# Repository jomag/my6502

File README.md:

# My 6502

I started watching [Ben Eaters](https://eater.net) [video series](https://eater.net/8bit)
where he builds a 6502 (actually, 65C02) based 8-bit computer from scratch
on breadboards. I thought it could be fun to follow along and build something similar,
but using real PCB's cause breadboards drive me crazy.

It might end up being something pretty to hang on the wall...

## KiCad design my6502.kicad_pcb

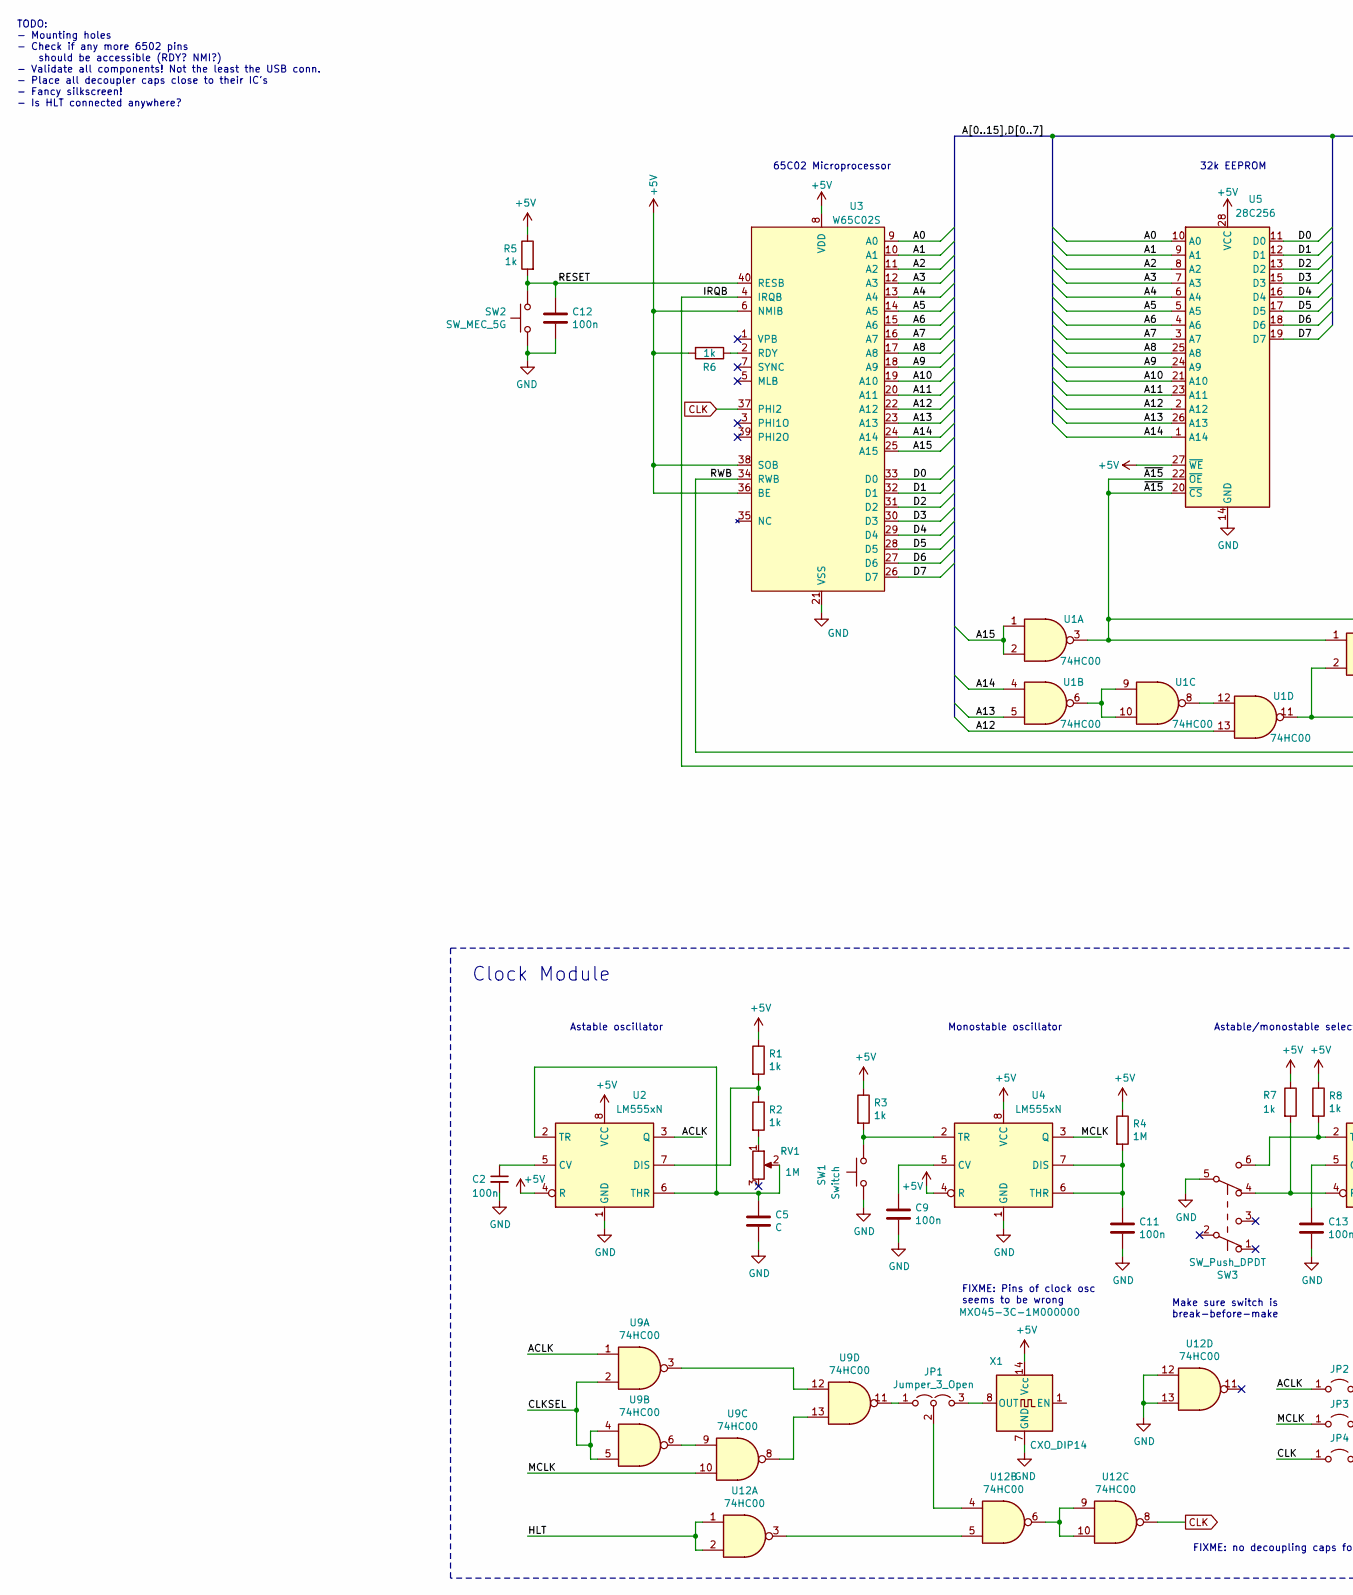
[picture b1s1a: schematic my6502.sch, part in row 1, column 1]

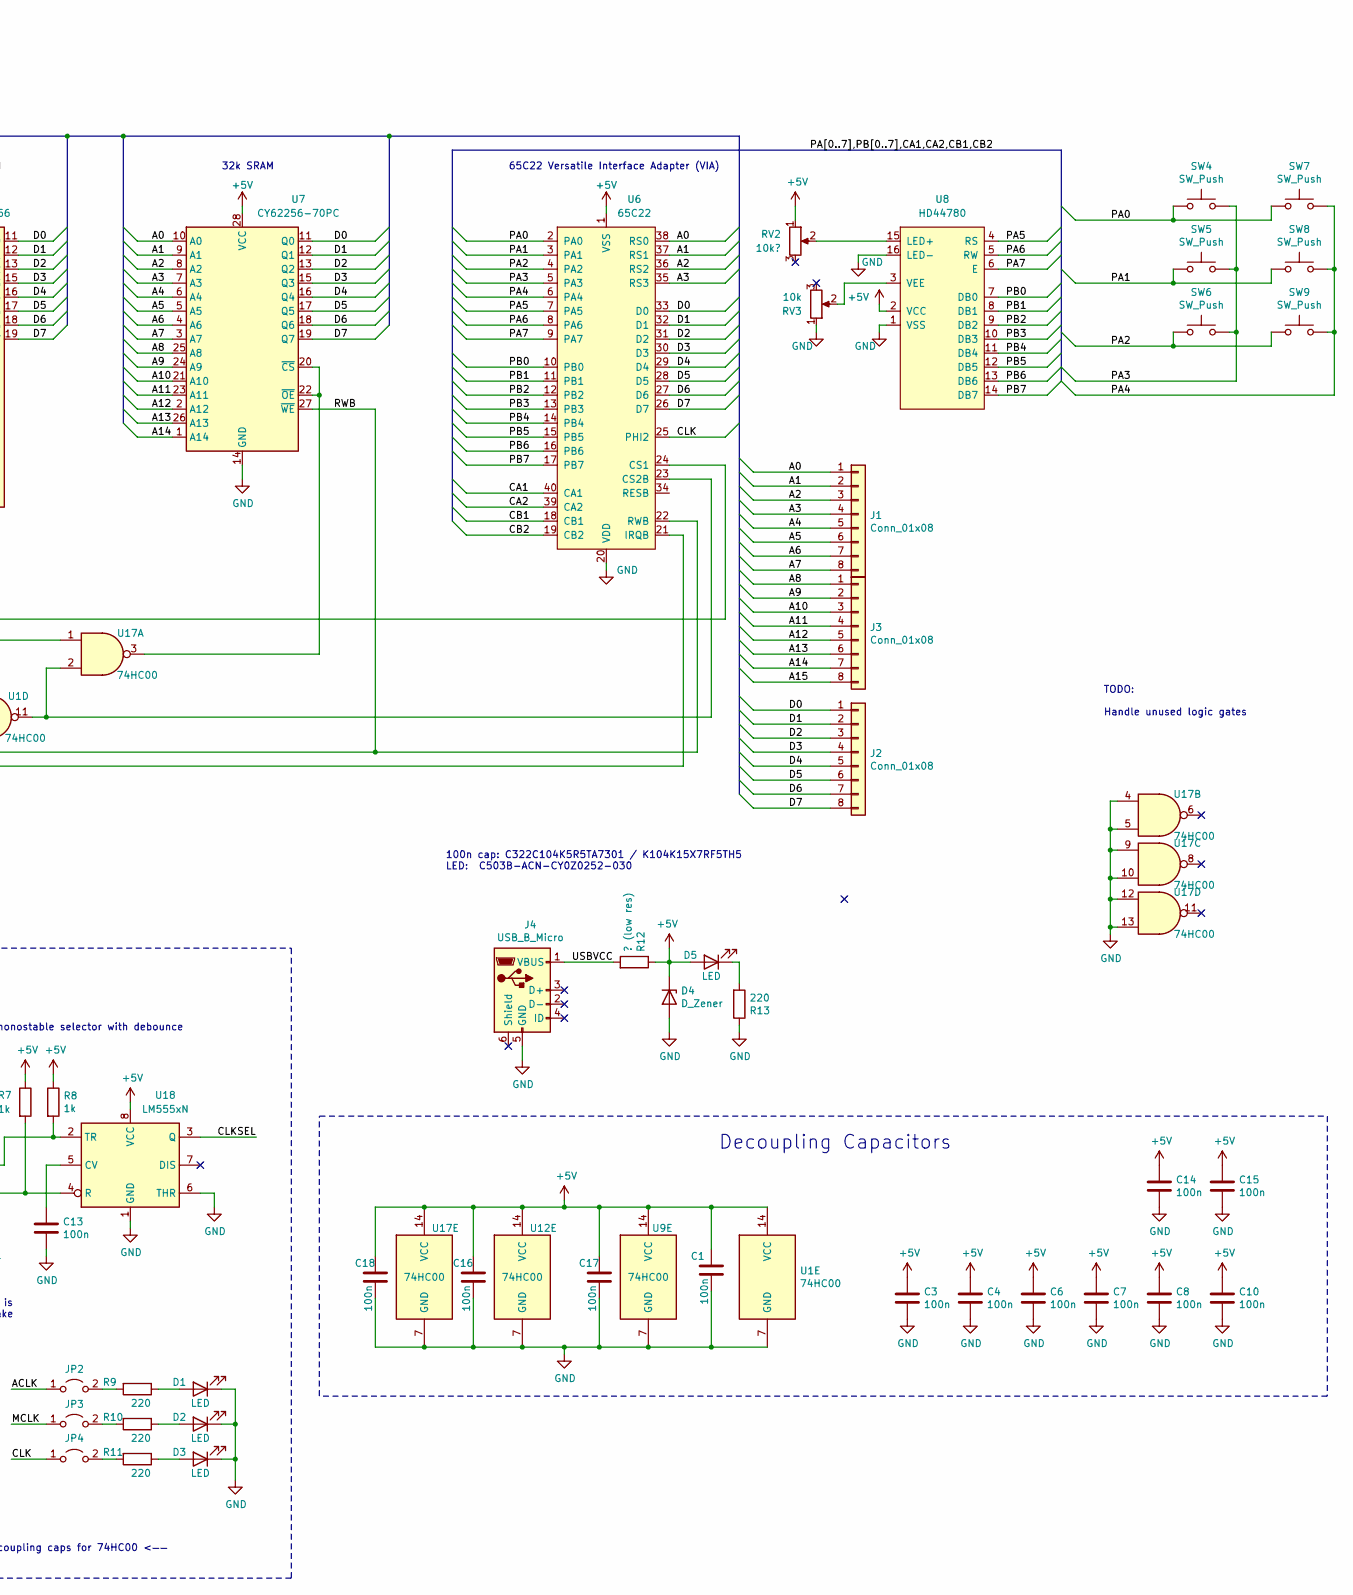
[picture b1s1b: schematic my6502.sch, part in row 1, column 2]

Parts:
C1, C2, C3, C4, C6, C7, C8, C9, C10, C11, C12, C13, C14, C15, C16, C17, C18: 100n; C_Disc_D5.1mm_W3.2mm_P5.00mm
C5: C
D1, D2, D3, D5: LED; LED_D3.0mm
D4: D_Zener; D_A-405_P7.62mm_Horizontal
J1, J2, J3: Conn_01x08; PinHeader_1x08_P2.54mm_Vertical
J4: USB_B_Micro; USB_Micro-B_Molex_47346-0001
JP1: Jumper_3_Open; PinHeader_1x03_P2.54mm_Vertical
JP2, JP3, JP4: Jumper_2_Open; PinHeader_1x02_P2.54mm_Vertical
R1, R2, R3, R5, R6, R7, R8: 1k; R_Axial_DIN0207_L6.3mm_D2.5mm_P7.62mm_Horizontal
R4: 1M; R_Axial_DIN0207_L6.3mm_D2.5mm_P7.62mm_Horizontal
R9, R10, R11, R13: 220; R_Axial_DIN0207_L6.3mm_D2.5mm_P7.62mm_Horizontal
R12: ? (low res); R_Axial_DIN0207_L6.3mm_D2.5mm_P7.62mm_Horizontal
RV1: 1M; Potentiometer_Bourns_3386F_Vertical; Digi-Key 3386X-1-105TLF-ND
RV2: 10k?; Potentiometer_Bourns_3296W_Vertical
RV3: 10k; Potentiometer_Bourns_3296W_Vertical
SW1: Switch; SW_PUSH_6mm
SW2: SW_MEC_5G; SW_PUSH_6mm
SW3: SW_Push_DPDT
SW4: SW_Push; SW_PUSH_6mm; PartID Adafruit 4183
SW5, SW6, SW7, SW8, SW9: SW_Push; SW_PUSH_6mm
U1, U9, U12, U17: 74HC00; DIP-14_W7.62mm_LongPads
U2, U4, U18: LM555xN; DIP-8_W7.62mm
U3: W65C02S; DIP-40_W15.24mm_Socket_LongPads
U5: 28C256; DIP-28_W15.24mm_Socket_LongPads
U6: 65C22; DIP-40_W15.24mm_Socket_LongPads
U7: CY62256-70PC; DIP-28_W15.24mm
U8: HD44780; WC1602A
X1: CXO_DIP14; Oscillator_DIP-14; MPN MXO45-3C-1M000000

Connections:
+5V: C1.1, C3.1, C4.1, C6.1, C7.1, C8.1, C10.1, C14.1, C15.1, C16.1, C17.1, C18.1, D4.1 (K), D5.2 (A), R1.1, R3.1, R4.1, R5.1, R6.2, R7.1, R8.1, R12.1, RV2.1, U1.14 (VCC), U2.4 (R), U2.8 (VCC), U3.6 (NMIB), U3.8 (VDD), U3.36 (BE), U3.38 (SOB), U4.4 (R), U4.8 (VCC), U5.27 (~WE), U5.28 (VCC), U6.1 (VSS), U7.28 (VCC), U8.2 (VCC), U9.14 (VCC), U12.14 (VCC), U17.14 (VCC), U18.8 (VCC), X1.14 (Vcc)
/A0: J1.1, U3.9 (A0), U5.10 (A0), U6.38 (RS0), U7.10 (A0)
/A1: J1.2, U3.10 (A1), U5.9 (A1), U6.37 (RS1), U7.9 (A1)
/A2: J1.3, U3.11 (A2), U5.8 (A2), U6.36 (RS2), U7.8 (A2)
/A3: J1.4, U3.12 (A3), U5.7 (A3), U6.35 (RS3), U7.7 (A3)
/A4: J1.5, U3.13 (A4), U5.6 (A4), U7.6 (A4)
/A5: J1.6, U3.14 (A5), U5.5 (A5), U7.5 (A5)
/A6: J1.7, U3.15 (A6), U5.4 (A6), U7.4 (A6)
/A7: J1.8, U3.16 (A7), U5.3 (A7), U7.3 (A7)
/A8: J3.1, U3.17 (A8), U5.25 (A8), U7.25 (A8)
/A9: J3.2, U3.18 (A9), U5.24 (A9), U7.24 (A9)
/A10: J3.3, U3.19 (A10), U5.21 (A10), U7.21 (A10)
/A11: J3.4, U3.20 (A11), U5.23 (A11), U7.23 (A11)
/A12: J3.5, U1.13, U3.22 (A12), U5.2 (A12), U7.2 (A12)
/A13: J3.6, U1.5, U3.23 (A13), U5.26 (A13), U7.26 (A13)
/A14: J3.7, U1.4, U3.24 (A14), U5.1 (A14), U7.1 (A14)
/A15: J3.8, U1.1, U1.2, U3.25 (A15)
/ACLK: JP2.1 (A), U2.3 (Q), U9.1
/CLKSEL: U9.2, U9.4, U9.5, U18.3 (Q)
/D0: J2.1, U3.33 (D0), U5.11 (D0), U6.33 (D0), U7.11 (Q0)
/D1: J2.2, U3.32 (D1), U5.12 (D1), U6.32 (D1), U7.12 (Q1)
/D2: J2.3, U3.31 (D2), U5.13 (D2), U6.31 (D2), U7.13 (Q2)
/D3: J2.4, U3.30 (D3), U5.15 (D3), U6.30 (D3), U7.15 (Q3)
/D4: J2.5, U3.29 (D4), U5.16 (D4), U6.29 (D4), U7.16 (Q4)
/D5: J2.6, U3.28 (D5), U5.17 (D5), U6.28 (D5), U7.17 (Q5)
/D6: J2.7, U3.27 (D6), U5.18 (D6), U6.27 (D6), U7.18 (Q6)
/D7: J2.8, U3.26 (D7), U5.19 (D7), U6.26 (D7), U7.19 (Q7)
/HLT: U12.1, U12.2
/IRQB: U3.4 (IRQB), U6.21 (IRQB)
/MCLK: JP3.1 (A), U4.3 (Q), U9.10
/PA0: SW4.1, SW7.1, U6.2 (PA0)
/PA1: SW5.1, SW8.1, U6.3 (PA1)
/PA2: SW6.1, SW9.1, U6.4 (PA2)
/PA3: SW4.2, SW5.2, SW6.2, U6.5 (PA3)
/PA4: SW7.2, SW8.2, SW9.2, U6.6 (PA4)
/PA5: U6.7 (PA5), U8.4 (RS)
/PA6: U6.8 (PA6), U8.5 (RW)
/PA7: U6.9 (PA7), U8.6 (E)
/PB0: U6.10 (PB0), U8.7 (DB0)
/PB1: U6.11 (PB1), U8.8 (DB1)
/PB2: U6.12 (PB2), U8.9 (DB2)
/PB3: U6.13 (PB3), U8.10 (DB3)
/PB4: U6.14 (PB4), U8.11 (DB4)
/PB5: U6.15 (PB5), U8.12 (DB5)
/PB6: U6.16 (PB6), U8.13 (DB6)
/PB7: U6.17 (PB7), U8.14 (DB7)
/RESET: C12.1, R5.2, SW2.1, U3.40 (RESB)
/RWB: U3.34 (RWB), U6.22 (RWB), U7.27 (~WE)
/USBVCC: J4.1 (VBUS), R12.2
/~A15: U1.3, U5.20 (~CS), U5.22 (~OE), U6.24 (CS1), U17.1
CLK: JP4.1 (A), U3.37 (PHI2), U6.25 (PHI2), U12.8
GND: C1.2, C2.2, C3.2, C4.2, C5.2, C6.2, C7.2, C8.2, C9.2, C10.2, C11.2, C12.2, C13.2, C14.2, C15.2, C16.2, C17.2, C18.2, D1.1 (K), D2.1 (K), D3.1 (K), D4.2 (A), J4.5 (GND), R13.1, RV3.1, SW1.1, SW2.2, SW3.5 (B), U1.7 (GND), U2.1 (GND), U3.21 (VSS), U4.1 (GND), U5.14 (GND), U6.20 (VDD), U7.14 (GND), U8.1 (VSS), U8.16 (LED-), U9.7 (GND), U12.7 (GND), U12.12, U12.13, U17.4, U17.5, U17.7 (GND), U17.9, U17.10, U17.12, U17.13, U18.1 (GND), U18.6 (THR), X1.7 (GND)
unnamed: C2.1, U2.5 (CV)
unnamed: C5.1, RV1.2, U2.2 (TR), U2.6 (THR)
unnamed: C9.1, U4.5 (CV)
unnamed: C11.1, R4.2, U4.6 (THR), U4.7 (DIS)
unnamed: C13.1, U18.5 (CV)
unnamed: D1.2 (A), R9.1
unnamed: D2.2 (A), R10.1
unnamed: D3.2 (A), R11.1
unnamed: D5.1 (K), R13.2
unnamed: JP1.1 (A), U9.11
unnamed: JP1.2 (C), U12.4
unnamed: JP1.3 (B), X1.8 (OUT)
unnamed: JP2.2 (B), R9.2
unnamed: JP3.2 (B), R10.2
unnamed: JP4.2 (B), R11.2
unnamed: R1.2, R2.1, U2.7 (DIS)
unnamed: R2.2, RV1.1
unnamed: R3.2, SW1.2, U4.2 (TR)
unnamed: R6.1, U3.2 (RDY)
unnamed: R7.2, SW3.4 (A), U18.4 (R)
unnamed: R8.2, SW3.6 (C), U18.2 (TR)
unnamed: RV2.2, U8.15 (LED+)
unnamed: RV3.2, U8.3 (VEE)
unnamed: U1.6, U1.9, U1.10
unnamed: U1.11, U6.23 (CS2B), U17.2
unnamed: U1.8, U1.12
unnamed: U9.6, U9.9
unnamed: U9.3, U9.12
unnamed: U9.8, U9.13
unnamed: U12.3, U12.5
unnamed: U12.6, U12.9, U12.10
unnamed: U7.20 (~CS), U7.22 (~OE), U17.3

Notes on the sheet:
Clock Module
Astable oscillator
Decoupling Capacitors
32k EEPROM
65C02 Microprocessor
65C22 Versatile Interface Adapter (VIA)
32k SRAM
TODO: Handle unused logic gates
Make sure switch is break-before-make
Astable/monostable selector with debounce
Monostable oscillator
FIXME: Pins of clock osc seems to be wrong
FIXME: no decoupling caps for 74HC00 <——
100n cap: C322C104K5R5TA7301 / K104K15X7RF5TH5 LED: C503B-ACN-CY0Z0252-030
TODO: - Mounting holes - Check if any more 6502 pins should be accessible (RDY? NMI?) - Validate all components! Not the least the USB conn. - Place all decoupler caps close to their IC's - Fancy silkscreen! - Is HLT connected anywhere?

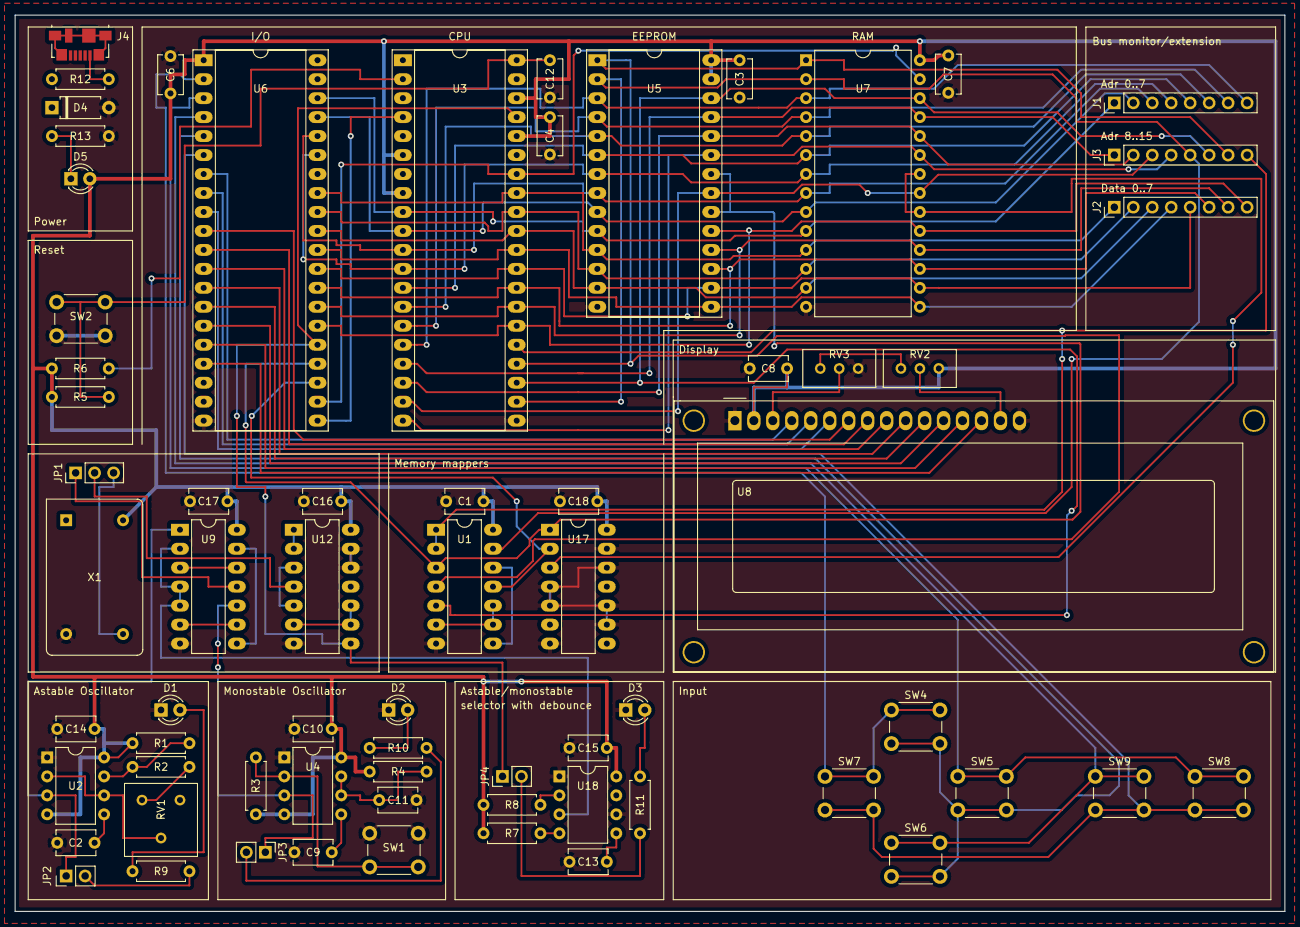
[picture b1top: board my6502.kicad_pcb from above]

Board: 4 copper layers, 170.0 x 120.0 mm, 67 parts (0 on the bottom side), 84 nets.

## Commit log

2021-01-20 Same state as at the end of Ben Eater video part 2
2021-01-21 Added VIA 65C22
2021-01-21 Add RAM
2021-01-22 Add minimal 555-based clock module
2021-01-23 Add manual clock pulse button (incomplete)
2021-01-23 Incomplete work on primarily display and keys
2021-02-13 Uncomitted changes
2021-04-18 Updates to the clock module
2021-04-22 Pick footprints for a many components
2021-05-16 placed most components
2021-05-25 USB connector, overvoltage protection, ...
2021-08-24 Mostly minor adjustments
2021-08-28 Some components decided on and initial routing
2021-08-28 Memory map (needs to be verified)
2021-08-29 More routing
2021-09-06 many routes
2021-09-11 only 3 routes remaining
